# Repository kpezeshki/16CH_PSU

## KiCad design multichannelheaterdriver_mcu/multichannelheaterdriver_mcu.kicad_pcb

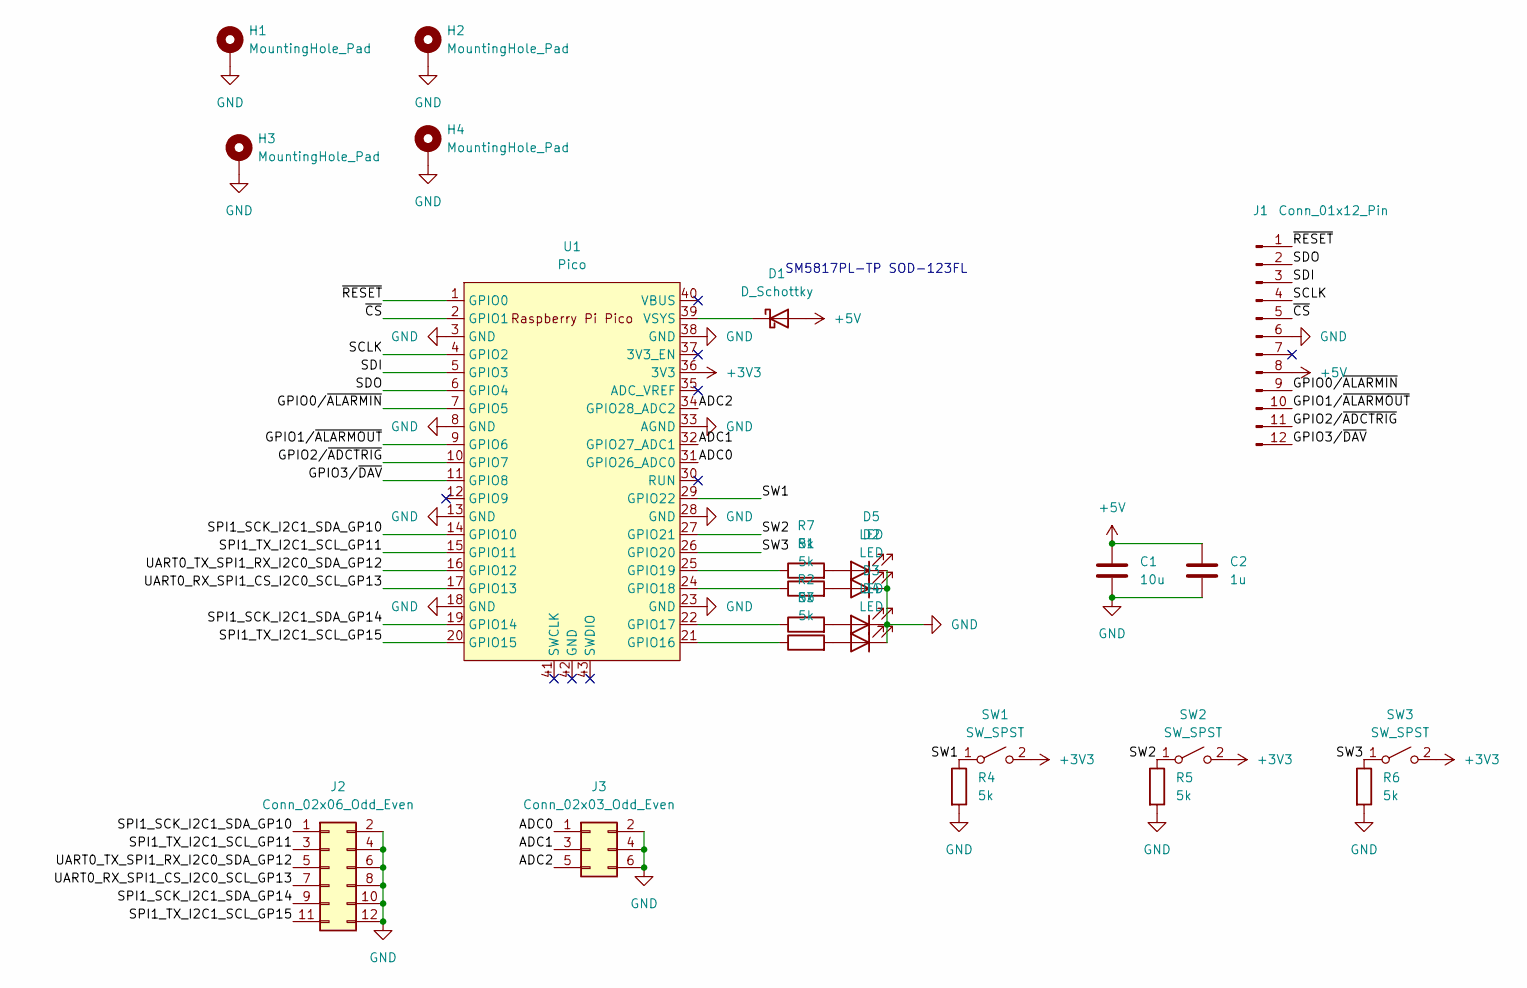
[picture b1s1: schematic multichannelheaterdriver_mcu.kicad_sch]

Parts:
C1: 10u; C_0805_2012Metric
C2: 1u; C_0805_2012Metric
D1: D_Schottky; D_SOD-123F
D2, D3, D4, D5: LED; LED_0805_2012Metric
H1, H2, H3, H4: MountingHole_Pad; MountingHole_3.2mm_M3_Pad
J1: Conn_01x12_Pin; PinHeader_1x12_P2.54mm_Vertical
J2: Conn_02x06_Odd_Even; PinHeader_2x06_P2.54mm_Horizontal
J3: Conn_02x03_Odd_Even; PinHeader_2x03_P2.54mm_Horizontal
R1, R2, R3, R4, R5, R6, R7: 5k; R_0805_2012Metric
SW1, SW2, SW3: SW_SPST; SW_Tactile_SPST_Angled_PTS645Vx31-2LFS
U1: Pico; RPi_Pico_SMD_TH

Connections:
+3V3: SW1.2 (B), SW2.2 (B), SW3.2 (B), U1.36 (3V3)
+5V: C1.1, C2.1, D1.2 (A), J1.8
/ADC0: J3.1, U1.31 (GPIO26_ADC0)
/ADC1: J3.3, U1.32 (GPIO27_ADC1)
/ADC2: J3.5, U1.34 (GPIO28_ADC2)
/GPIO0/~ALARMIN: J1.9, U1.7 (GPIO5)
/GPIO1/~ALARMOUT: J1.10, U1.9 (GPIO6)
/GPIO2/~ADCTRIG: J1.11, U1.10 (GPIO7)
/GPIO3/~DAV: J1.12, U1.11 (GPIO8)
/SCLK: J1.4, U1.4 (GPIO2)
/SDI: J1.3, U1.5 (GPIO3)
/SDO: J1.2, U1.6 (GPIO4)
/SPI1_SCK_I2C1_SDA_GP10: J2.1, U1.14 (GPIO10)
/SPI1_SCK_I2C1_SDA_GP14: J2.9, U1.19 (GPIO14)
/SPI1_TX_I2C1_SCL_GP11: J2.3, U1.15 (GPIO11)
/SPI1_TX_I2C1_SCL_GP15: J2.11, U1.20 (GPIO15)
/SW1: R4.1, SW1.1 (A), U1.29 (GPIO22)
/SW2: R5.1, SW2.1 (A), U1.27 (GPIO21)
/SW3: R6.1, SW3.1 (A), U1.26 (GPIO20)
/UART0_RX_SPI1_CS_I2C0_SCL_GP13: J2.7, U1.17 (GPIO13)
/UART0_TX_SPI1_RX_I2C0_SDA_GP12: J2.5, U1.16 (GPIO12)
/~CS: J1.5, U1.2 (GPIO1)
/~RESET: J1.1, U1.1 (GPIO0)
GND: C1.2, C2.2, D2.1 (K), D3.1 (K), D4.1 (K), D5.1 (K), H1.1, H2.1, H3.1, H4.1, J1.6, J2.2, J2.4, J2.6, J2.8, J2.10, J2.12, J3.2, J3.4, J3.6, R4.2, R5.2, R6.2, U1.3 (GND), U1.8 (GND), U1.13 (GND), U1.18 (GND), U1.23 (GND), U1.28 (GND), U1.33 (AGND), U1.38 (GND)
unnamed: D1.1 (K), U1.39 (VSYS)
unnamed: D2.2 (A), R1.2
unnamed: D3.2 (A), R2.2
unnamed: D4.2 (A), R3.2
unnamed: D5.2 (A), R7.2
unnamed: R3.1, U1.21 (GPIO16)
unnamed: R2.1, U1.22 (GPIO17)
unnamed: R1.1, U1.24 (GPIO18)
unnamed: R7.1, U1.25 (GPIO19)

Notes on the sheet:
SM5817PL-TP SOD-123FL

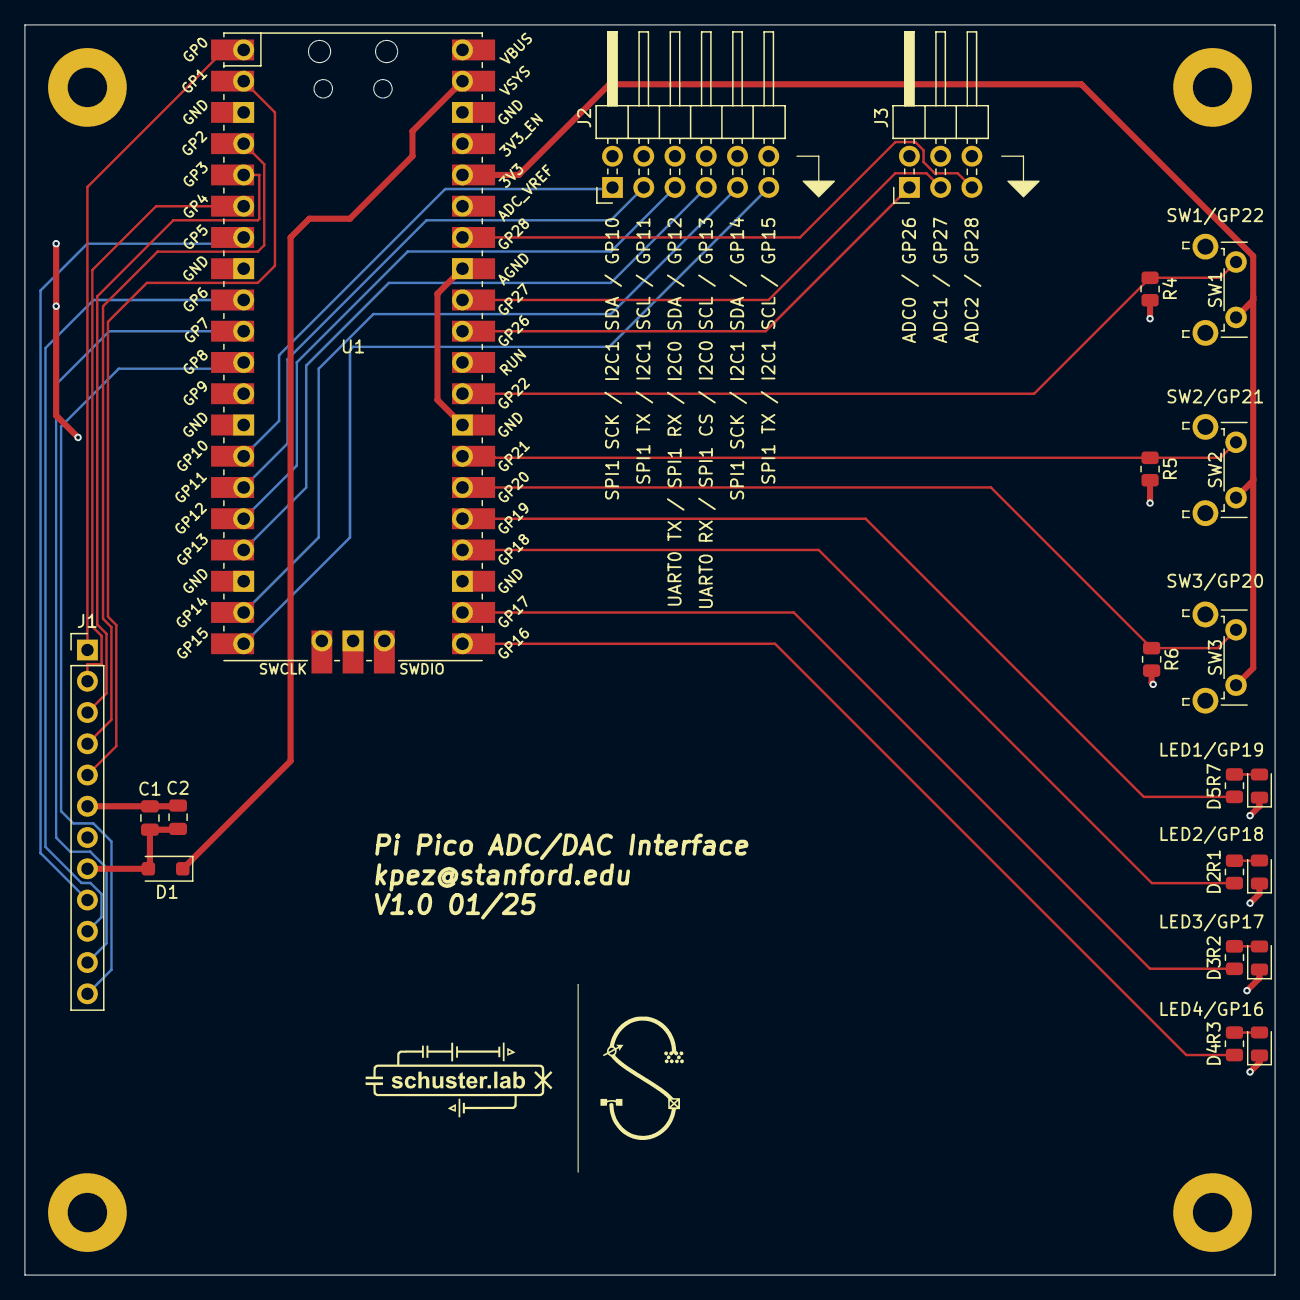
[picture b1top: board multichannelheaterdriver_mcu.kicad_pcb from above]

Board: 2 copper layers, 101.6 x 101.6 mm, 25 parts (0 on the bottom side), 33 nets.

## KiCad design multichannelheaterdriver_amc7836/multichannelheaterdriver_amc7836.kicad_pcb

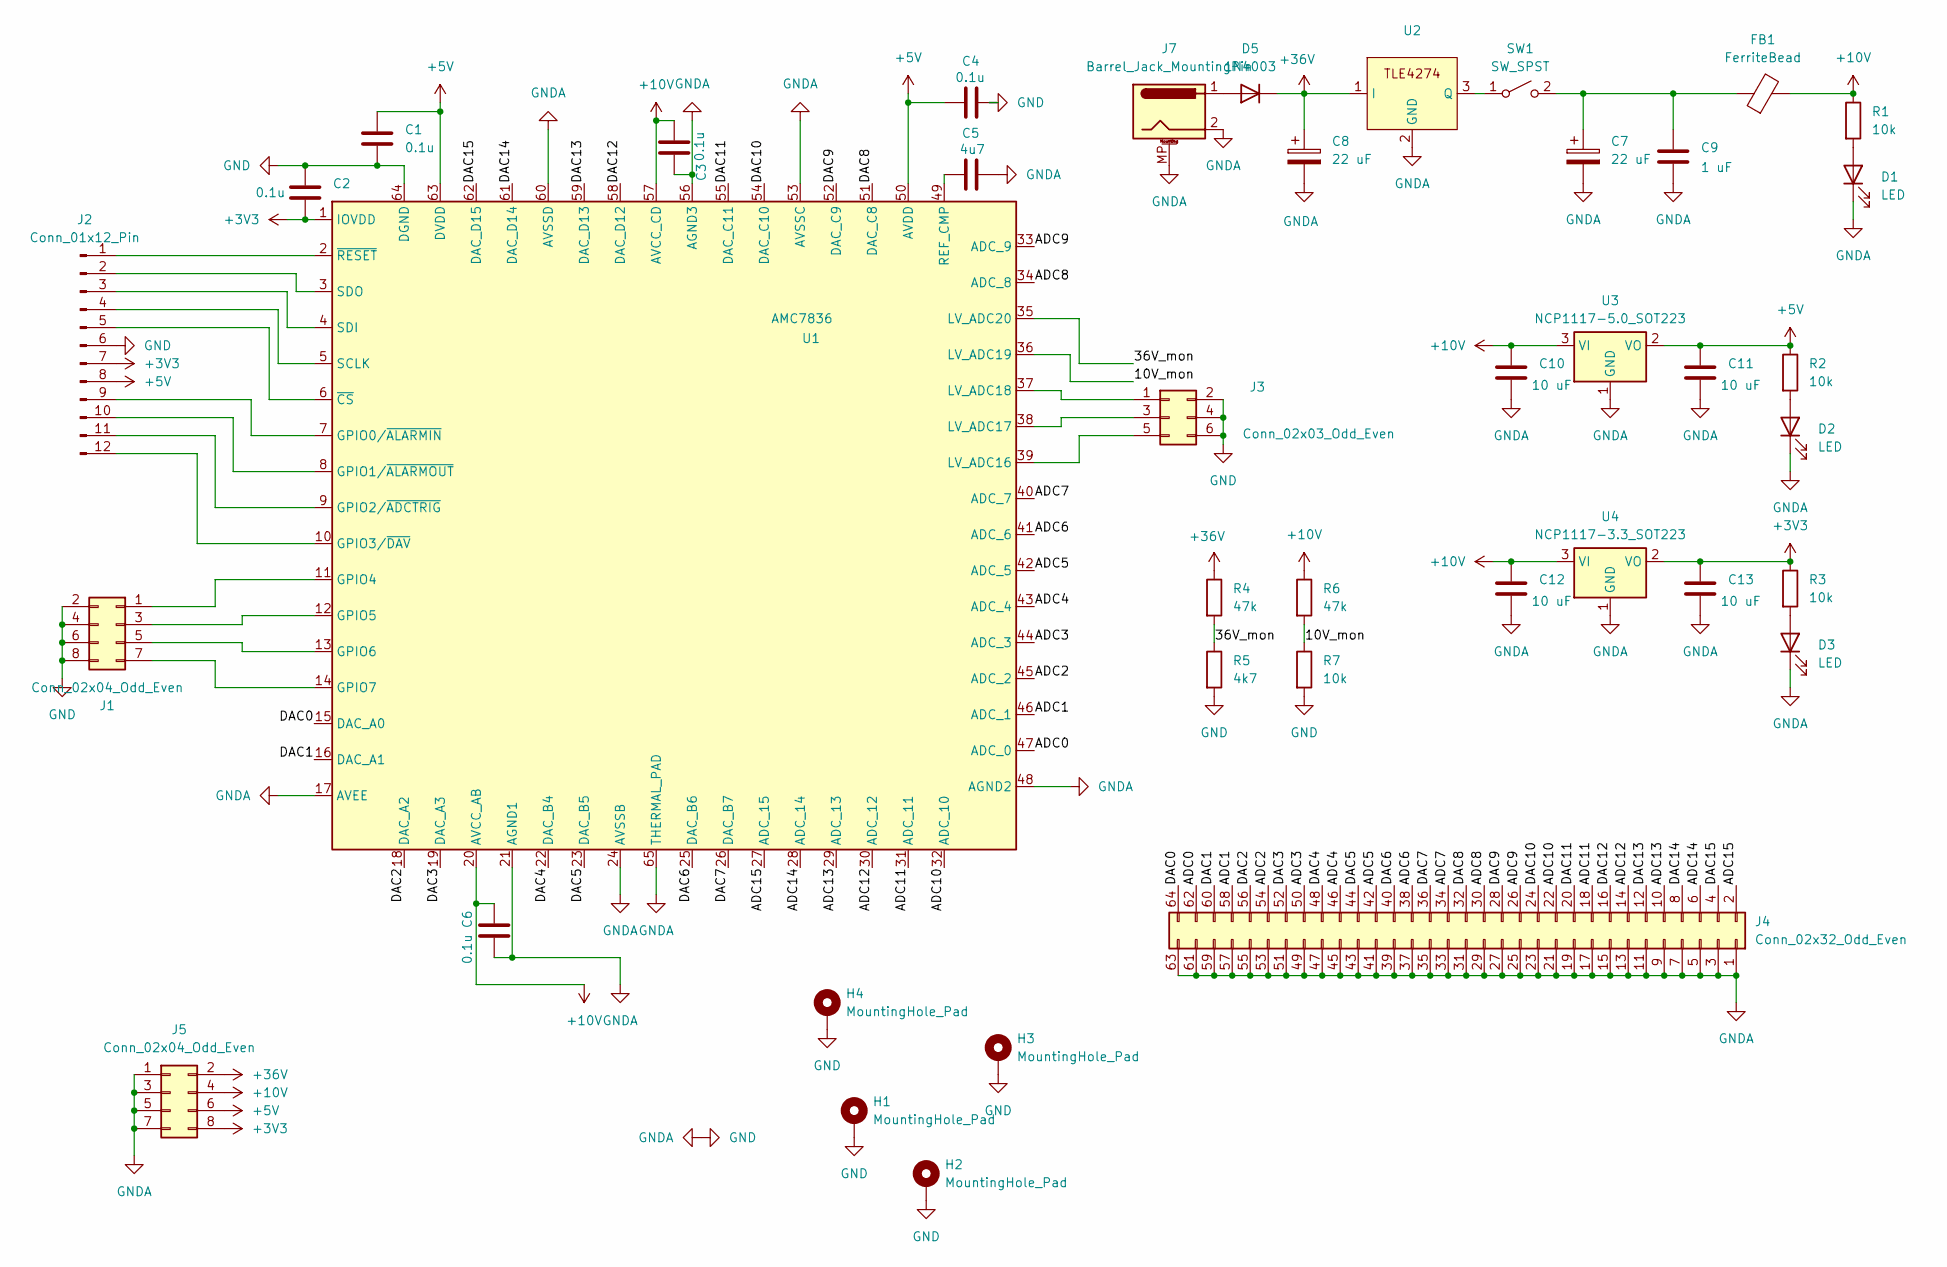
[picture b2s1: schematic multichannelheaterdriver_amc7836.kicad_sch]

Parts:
C1, C2, C3, C4, C6: 0.1u; C_0805_2012Metric
C5: 4u7; C_0805_2012Metric
C7, C8: 22 uF; CP_Radial_D6.3mm_P2.50mm
C9: 1 uF; C_0805_2012Metric
C10, C11, C12, C13: 10 uF; C_0805_2012Metric
D1, D2, D3: LED; LED_0805_2012Metric_Pad1.15x1.40mm_HandSolder
D5: 1N4003; D_DO-41_SOD81_P10.16mm_Horizontal
FB1: FerriteBead; R_0805_2012Metric
H1, H2, H3, H4: MountingHole_Pad; MountingHole_3.2mm_M3_Pad
J1: Conn_02x04_Odd_Even; PinHeader_2x04_P2.54mm_Horizontal
J2: Conn_01x12_Pin; PinHeader_1x12_P2.54mm_Vertical
J3: Conn_02x03_Odd_Even; PinHeader_2x03_P2.54mm_Horizontal
J4: Conn_02x32_Odd_Even; PinHeader_2x32_P2.54mm_Vertical
J5: Conn_02x04_Odd_Even; PinHeader_2x04_P2.54mm_Vertical
J7: Barrel_Jack_MountingPin; BarrelJack_CUI_PJ-063AH_Horizontal
R1, R2, R3, R7: 10k; R_0805_2012Metric
R4, R6: 47k; R_0805_2012Metric
R5: 4k7; R_0805_2012Metric
SW1: SW_SPST; PinHeader_1x02_P2.54mm_Horizontal
U1: AMC7836; IC_AMC7812BSPAP
U2: TO-252-3_TabPin2
U3: NCP1117-5.0_SOT223; SOT-223-3_TabPin2
U4: NCP1117-3.3_SOT223; SOT-223-3_TabPin2

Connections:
+3V3: C2.2, C13.1, J2.7, J5.8, R3.1, U1.1 (IOVDD), U4.2 (VO)
+5V: C1.1, C4.1, C11.1, J2.8, J5.6, R2.1, U1.50 (AVDD), U1.63 (DVDD), U3.2 (VO)
+10V: C3.1, C6.1, C10.1, C12.1, FB1.2, J5.4, R1.1, R6.1, U1.20 (AVCC_AB), U1.57 (AVCC_CD), U3.3 (VI), U4.3 (VI)
+36V: C8.1, D5.1 (K), J5.2, R4.1, U2.1 (I)
/10V_mon: R6.2, R7.1, U1.36 (LV_ADC19)
/36V_mon: R4.2, R5.1, U1.35 (LV_ADC20)
/ADC0: J4.62, U1.47 (ADC_0)
/ADC1: J4.58, U1.46 (ADC_1)
/ADC2: J4.54, U1.45 (ADC_2)
/ADC3: J4.50, U1.44 (ADC_3)
/ADC4: J4.46, U1.43 (ADC_4)
/ADC5: J4.42, U1.42 (ADC_5)
/ADC6: J4.38, U1.41 (ADC_6)
/ADC7: J4.34, U1.40 (ADC_7)
/ADC8: J4.30, U1.34 (ADC_8)
/ADC9: J4.26, U1.33 (ADC_9)
/ADC10: J4.22, U1.32 (ADC_10)
/ADC11: J4.18, U1.31 (ADC_11)
/ADC12: J4.14, U1.30 (ADC_12)
/ADC13: J4.10, U1.29 (ADC_13)
/ADC14: J4.6, U1.28 (ADC_14)
/ADC15: J4.2, U1.27 (ADC_15)
/DAC0: J4.64, U1.15 (DAC_A0)
/DAC1: J4.60, U1.16 (DAC_A1)
/DAC2: J4.56, U1.18 (DAC_A2)
/DAC3: J4.52, U1.19 (DAC_A3)
/DAC4: J4.48, U1.22 (DAC_B4)
/DAC5: J4.44, U1.23 (DAC_B5)
/DAC6: J4.40, U1.25 (DAC_B6)
/DAC7: J4.36, U1.26 (DAC_B7)
/DAC8: J4.32, U1.51 (DAC_C8)
/DAC9: J4.28, U1.52 (DAC_C9)
/DAC10: J4.24, U1.54 (DAC_C10)
/DAC11: J4.20, U1.55 (DAC_C11)
/DAC12: J4.16, U1.58 (DAC_D12)
/DAC13: J4.12, U1.59 (DAC_D13)
/DAC14: J4.8, U1.61 (DAC_D14)
/DAC15: J4.4, U1.62 (DAC_D15)
GND: C1.2, C2.1, C3.2, C4.2, C5.2, C6.2, C7.2, C8.2, C9.2, C10.2, C11.2, C12.2, C13.2, D1.1 (K), D2.1 (K), D3.1 (K), H1.1, H2.1, H3.1, H4.1, J1.2, J1.4, J1.6, J1.8, J2.6, J3.2, J3.4, J3.6, J4.1, J4.3, J4.5, J4.7, J4.9, J4.11, J4.13, J4.15, J4.17, J4.19, J4.21, J4.23, J4.25, J4.27, J4.29, J4.31, J4.33, J4.35, J4.37, J4.39, J4.41, J4.43, J4.45, J4.47, J4.49, J4.51, J4.53, J4.55, J4.57, J4.59, J4.61, J4.63, J5.1, J5.3, J5.5, J5.7, J7.2, J7.MP (MountPin), R5.2, R7.2, U1.17 (AVEE), U1.21 (AGND1), U1.24 (AVSSB), U1.48 (AGND2), U1.53 (AVSSC), U1.56 (AGND3), U1.60 (AVSSD), U1.64 (DGND), U1.65 (THERMAL_PAD), U2.2 (GND), U3.1 (GND), U4.1 (GND)
unnamed: D1.2 (A), R1.2
unnamed: D2.2 (A), R2.2
unnamed: D3.2 (A), R3.2
unnamed: D5.2 (A), J7.1
unnamed: J1.1, U1.11 (GPIO4)
unnamed: J1.3, U1.12 (GPIO5)
unnamed: J1.5, U1.13 (GPIO6)
unnamed: J1.7, U1.14 (GPIO7)
unnamed: J2.1, U1.2 (~RESET)
unnamed: J2.2, U1.3 (SDO)
unnamed: J2.3, U1.4 (SDI)
unnamed: J2.4, U1.5 (SCLK)
unnamed: J2.5, U1.6 (~CS)
unnamed: J2.9, U1.7 (GPIO0/~ALARMIN)
unnamed: J2.10, U1.8 (GPIO1/~ALARMOUT)
unnamed: J2.11, U1.9 (GPIO2/~ADCTRIG)
unnamed: J2.12, U1.10 (GPIO3/~DAV)
unnamed: J3.1, U1.37 (LV_ADC18)
unnamed: J3.3, U1.38 (LV_ADC17)
unnamed: J3.5, U1.39 (LV_ADC16)
unnamed: SW1.1 (A), U2.3 (Q)
unnamed: C7.1, C9.1, FB1.1, SW1.2 (B)
unnamed: C5.1, U1.49 (REF_CMP)

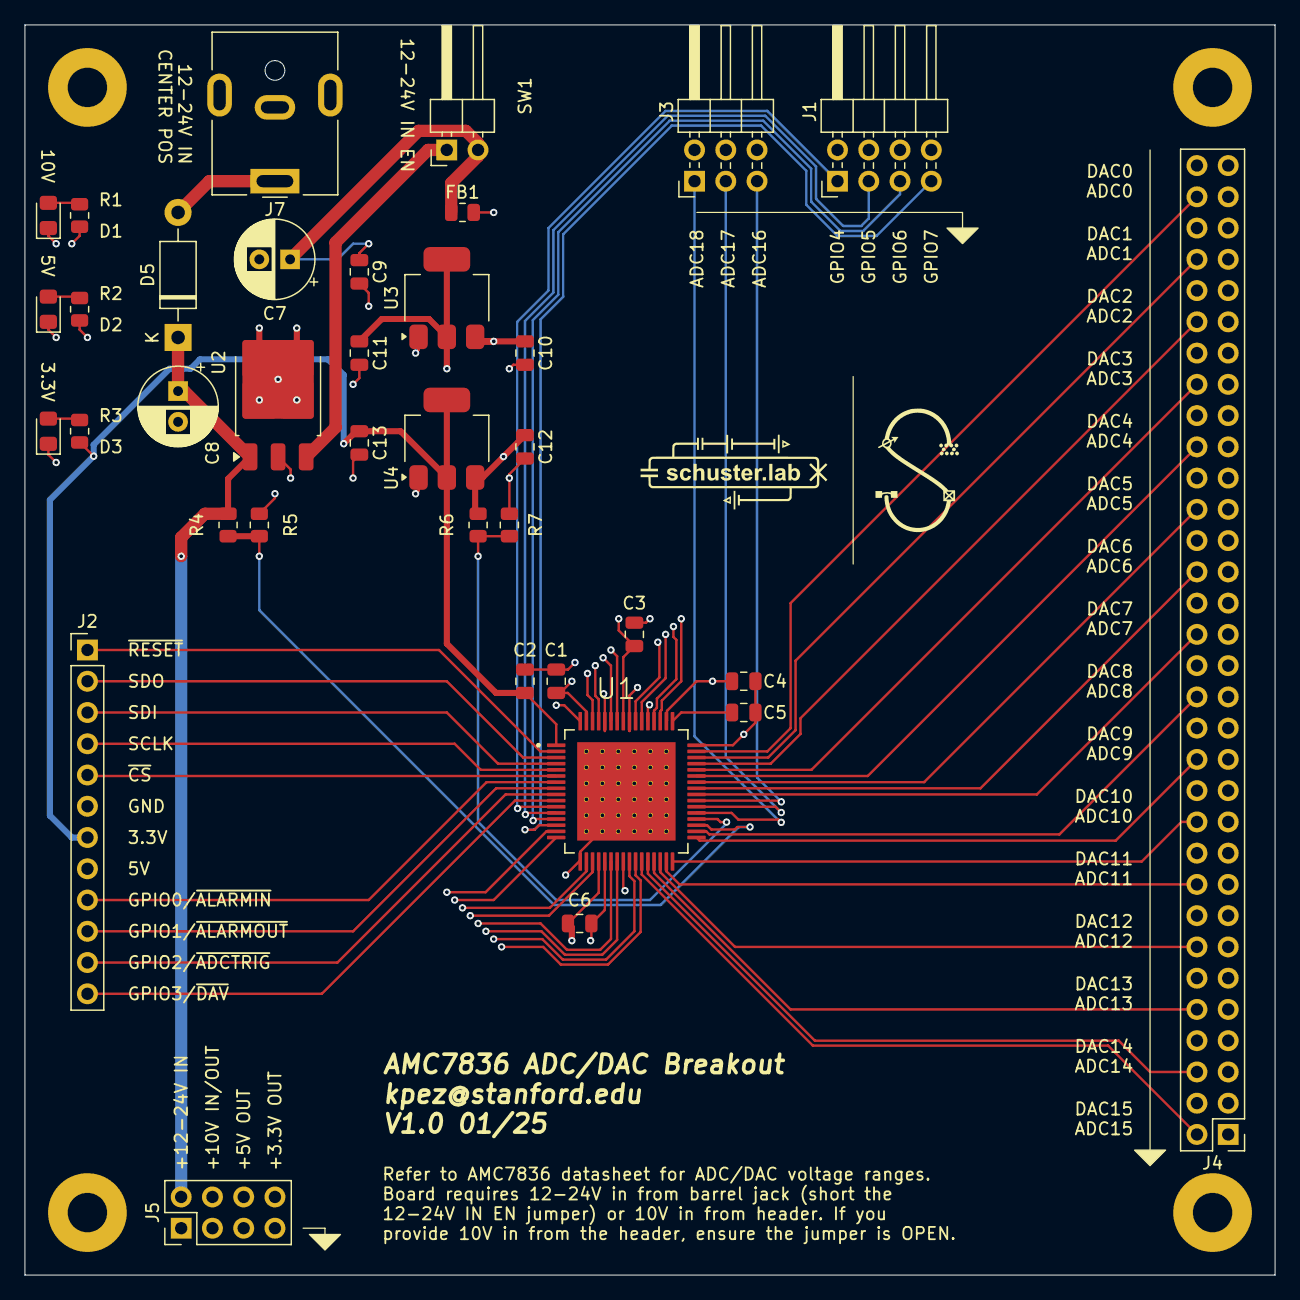
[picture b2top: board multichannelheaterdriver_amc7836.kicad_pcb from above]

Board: 6 copper layers, 101.6 x 101.6 mm, 40 parts (0 on the bottom side), 62 nets.

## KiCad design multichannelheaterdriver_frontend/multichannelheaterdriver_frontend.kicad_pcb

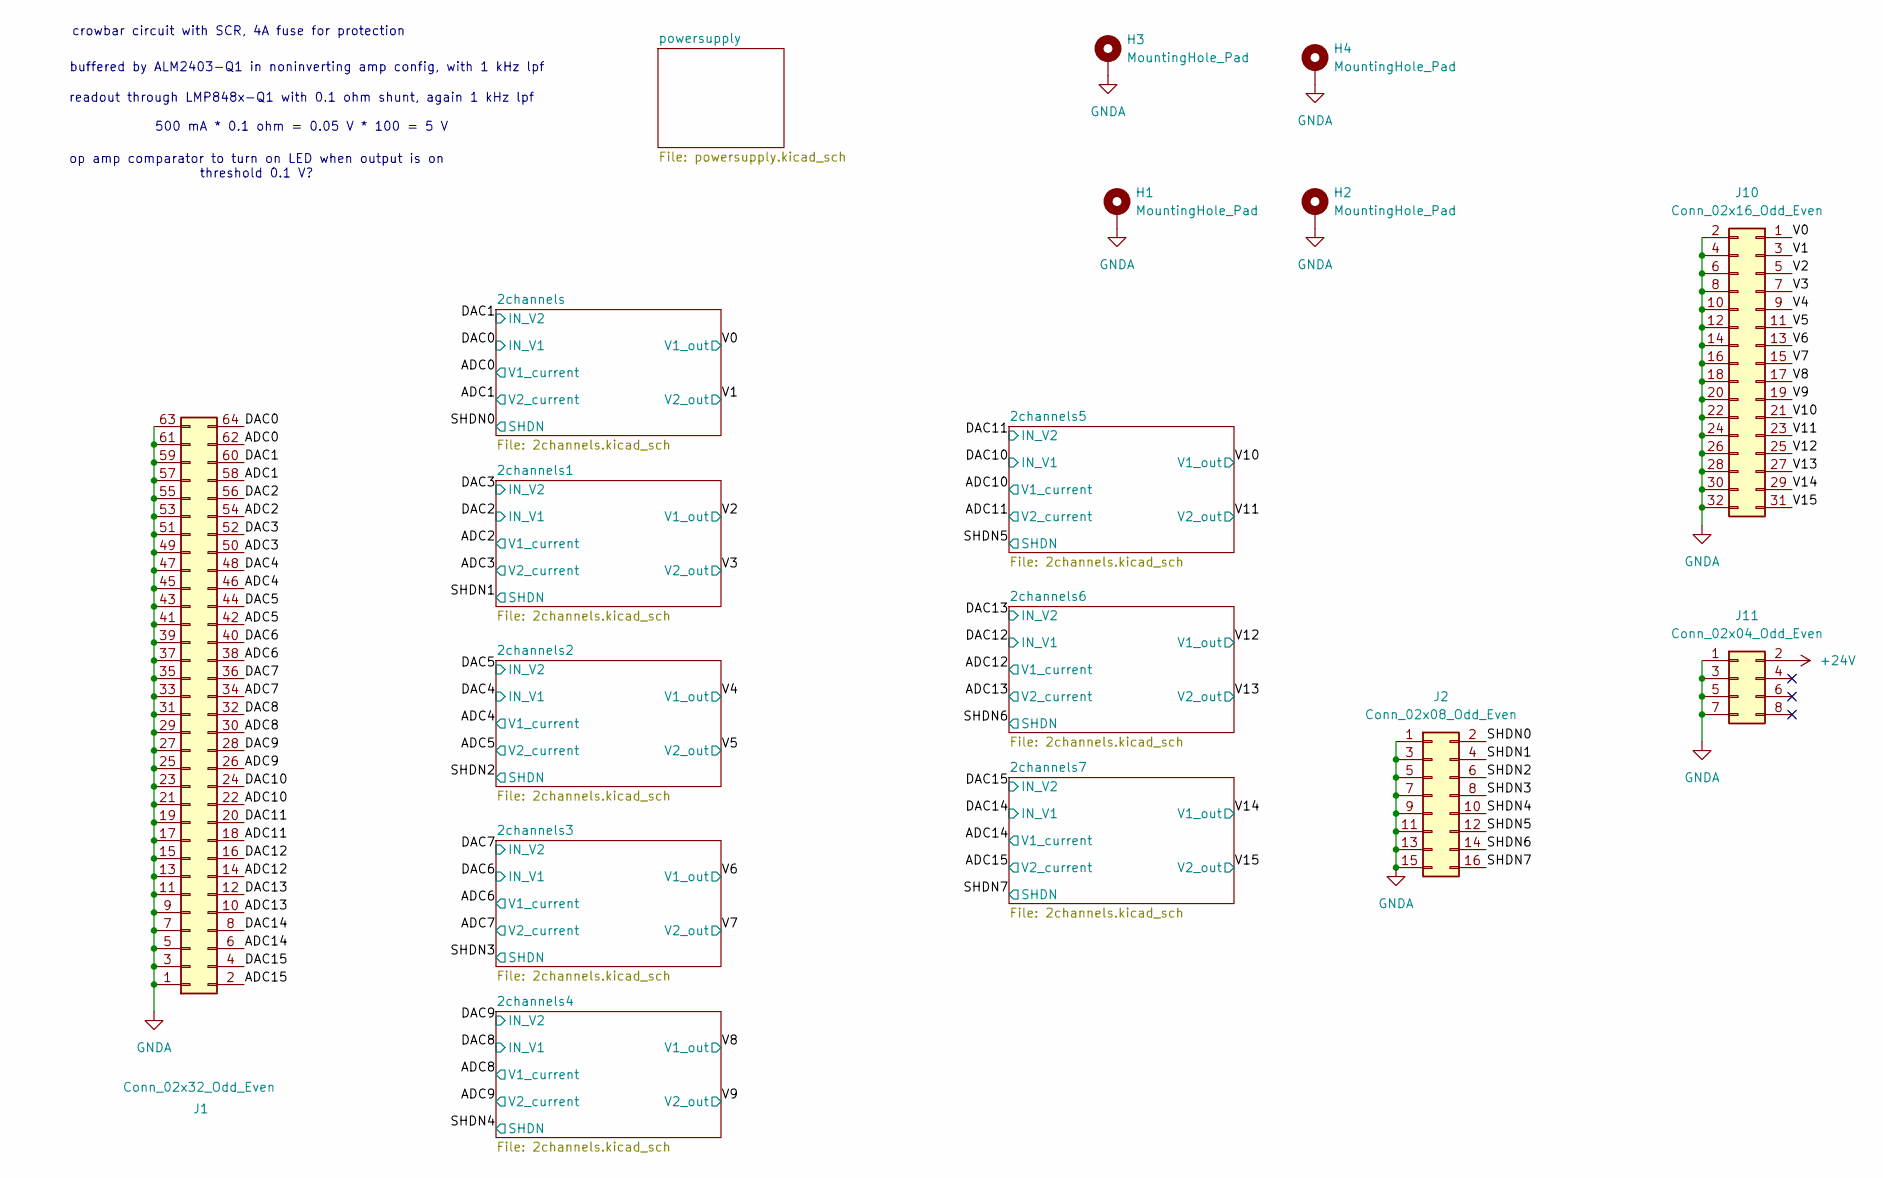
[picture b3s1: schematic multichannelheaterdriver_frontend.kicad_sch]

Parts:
H1, H2, H3, H4: MountingHole_Pad; MountingHole_3.2mm_M3_Pad
J1: Conn_02x32_Odd_Even; PinHeader_2x32_P2.54mm_Vertical
J2: Conn_02x08_Odd_Even; PinHeader_2x08_P2.54mm_Vertical
J10: Conn_02x16_Odd_Even; PinHeader_2x16_P2.54mm_Horizontal
J11: Conn_02x04_Odd_Even; PinHeader_2x04_P2.54mm_Vertical

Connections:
+24V: J11.2; also elsewhere on the board
/ADC0: J1.62; also elsewhere on the board
/ADC1: J1.58; also elsewhere on the board
/ADC2: J1.54; also elsewhere on the board
/ADC3: J1.50; also elsewhere on the board
/ADC4: J1.46; also elsewhere on the board
/ADC5: J1.42; also elsewhere on the board
/ADC6: J1.38; also elsewhere on the board
/ADC7: J1.34; also elsewhere on the board
/ADC8: J1.30; also elsewhere on the board
/ADC9: J1.26; also elsewhere on the board
/ADC10: J1.22; also elsewhere on the board
/ADC11: J1.18; also elsewhere on the board
/ADC12: J1.14; also elsewhere on the board
/ADC13: J1.10; also elsewhere on the board
/ADC14: J1.6; also elsewhere on the board
/ADC15: J1.2; also elsewhere on the board
/DAC0: J1.64; also elsewhere on the board
/DAC1: J1.60; also elsewhere on the board
/DAC2: J1.56; also elsewhere on the board
/DAC3: J1.52; also elsewhere on the board
/DAC4: J1.48; also elsewhere on the board
/DAC5: J1.44; also elsewhere on the board
/DAC6: J1.40; also elsewhere on the board
/DAC7: J1.36; also elsewhere on the board
/DAC8: J1.32; also elsewhere on the board
/DAC9: J1.28; also elsewhere on the board
/DAC10: J1.24; also elsewhere on the board
/DAC11: J1.20; also elsewhere on the board
/DAC12: J1.16; also elsewhere on the board
/DAC13: J1.12; also elsewhere on the board
/DAC14: J1.8; also elsewhere on the board
/DAC15: J1.4; also elsewhere on the board
/SHDN0: J2.2; also elsewhere on the board
/SHDN1: J2.4; also elsewhere on the board
/SHDN2: J2.6; also elsewhere on the board
/SHDN3: J2.8; also elsewhere on the board
/SHDN4: J2.10; also elsewhere on the board
/SHDN5: J2.12; also elsewhere on the board
/SHDN6: J2.14; also elsewhere on the board
/SHDN7: J2.16; also elsewhere on the board
/V0: J10.1; also elsewhere on the board
/V1: J10.3; also elsewhere on the board
/V2: J10.5; also elsewhere on the board
/V3: J10.7; also elsewhere on the board
/V4: J10.9; also elsewhere on the board
/V5: J10.11; also elsewhere on the board
/V6: J10.13; also elsewhere on the board
/V7: J10.15; also elsewhere on the board
/V8: J10.17; also elsewhere on the board
/V9: J10.19; also elsewhere on the board
/V10: J10.21; also elsewhere on the board
/V11: J10.23; also elsewhere on the board
/V12: J10.25; also elsewhere on the board
/V13: J10.27; also elsewhere on the board
/V14: J10.29; also elsewhere on the board
/V15: J10.31; also elsewhere on the board
GNDA: H1.1, H2.1, H3.1, H4.1, J1.1, J1.3, J1.5, J1.7, J1.9, J1.11, J1.13, J1.15, J1.17, J1.19, J1.21, J1.23, J1.25, J1.27, J1.29, J1.31, J1.33, J1.35, J1.37, J1.39, J1.41, J1.43, J1.45, J1.47, J1.49, J1.51, J1.53, J1.55, J1.57, J1.59, J1.61, J1.63, J2.1, J2.3, J2.5, J2.7, J2.9, J2.11, J2.13, J2.15, J10.2, J10.4, J10.6, J10.8, J10.10, J10.12, J10.14, J10.16, J10.18, J10.20, J10.22, J10.24, J10.26, J10.28, J10.30, J10.32, J11.1, J11.3, J11.5, J11.7; also elsewhere on the board

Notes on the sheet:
op amp comparator to turn on LED when output is on threshold 0.1 V?
buffered by ALM2403-Q1 in noninverting amp config, with 1 kHz lpf
crowbar circuit with SCR, 4A fuse for protection
readout through LMP848x-Q1 with 0.1 ohm shunt, again 1 kHz lpf 500 mA * 0.1 ohm = 0.05 V * 100 = 5 V

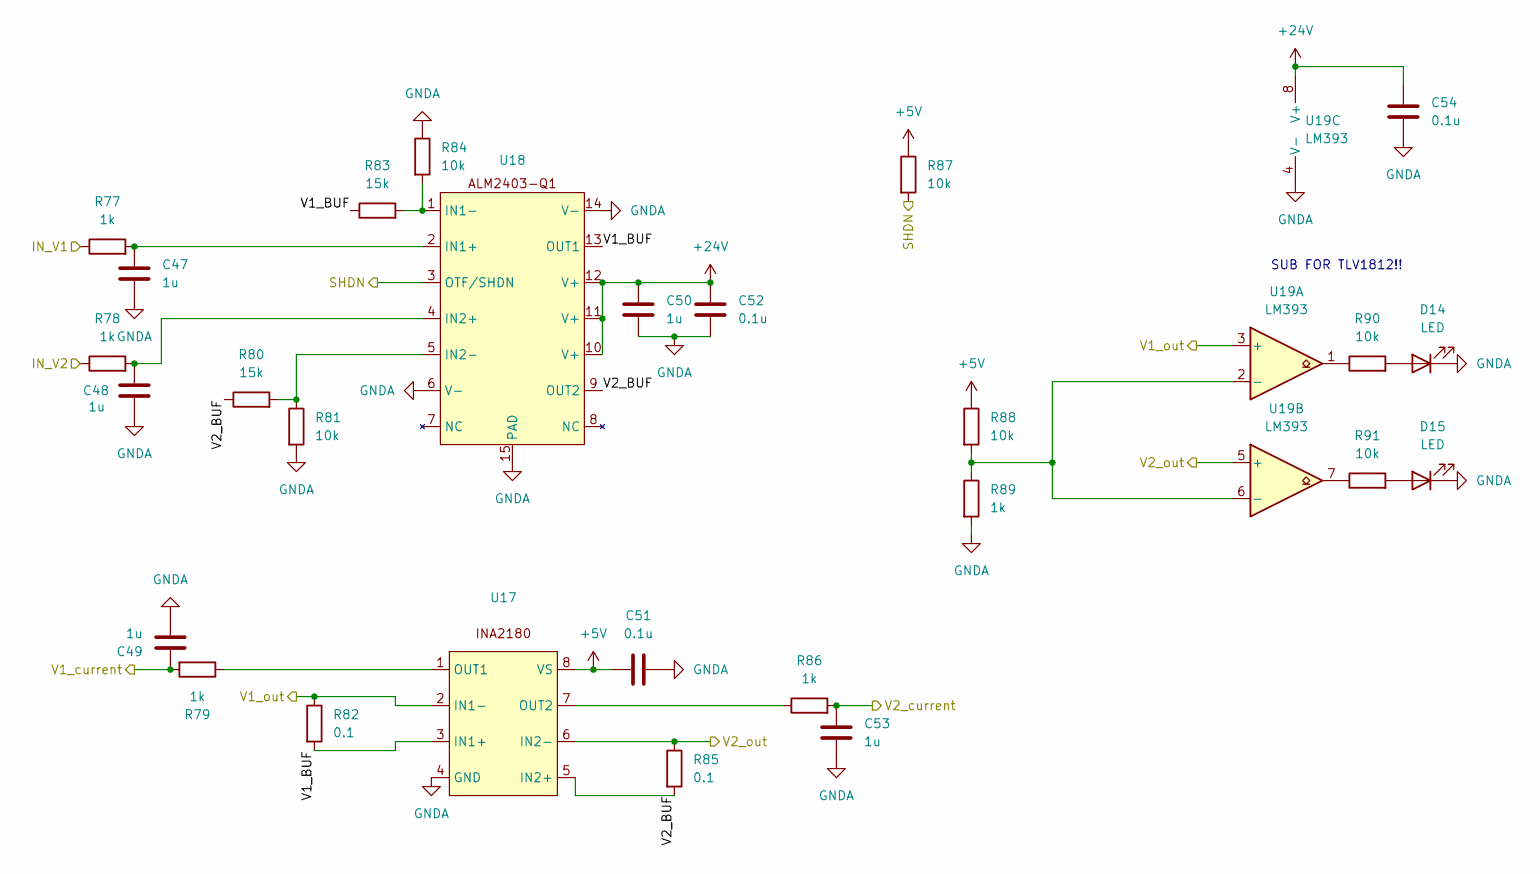
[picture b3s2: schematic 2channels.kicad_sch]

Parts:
C47, C48, C49, C50, C53: 1u; C_0603_1608Metric
C51, C52, C54: 0.1u; C_0603_1608Metric
D14, D15: LED; LED_0805_2012Metric
R77, R78, R79, R86, R89: 1k; R_0603_1608Metric
R80, R83: 15k; R_0603_1608Metric
R81, R84, R87, R88, R90, R91: 10k; R_0603_1608Metric
R82, R85: 0.1; R_0603_1608Metric
U17: VSSOP-8_3x3mm_P0.65mm
U18: IC_TPS27S100BPWPR
U19: LM393; SOIC-8_3.9x4.9mm_P1.27mm

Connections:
+5V: C51.1, R87.1, R88.1, U17.8 (VS); also elsewhere on the board
+24V: C50.1, C52.1, C54.1, U18.10 (V+), U18.11 (V+), U18.12 (V+), U19.8 (V+); also elsewhere on the board
/2channels5/V1_BUF: R82.2, R83.1, U17.3 (IN1+), U18.13 (OUT1)
/2channels5/V2_BUF: R80.1, R85.2, U17.5 (IN2+), U18.9 (OUT2)
/ADC10: C49.1, R79.2; also elsewhere on the board
/ADC11: C53.1, R86.2; also elsewhere on the board
/DAC10: R77.1; also elsewhere on the board
/DAC11: R78.1; also elsewhere on the board
/SHDN5: R87.2, U18.3 (OTF/SHDN); also elsewhere on the board
/V10: R82.1, U17.2 (IN1-), U19.3 (+); also elsewhere on the board
/V11: R85.1, U17.6 (IN2-), U19.5 (+); also elsewhere on the board
GNDA: C47.2, C48.2, C49.2, C50.2, C51.2, C52.2, C53.2, C54.2, D14.1 (K), D15.1 (K), R81.2, R84.1, R89.2, U17.4 (GND), U18.6 (V-), U18.14 (V-), U18.15 (PAD), U19.4 (V-); also elsewhere on the board
unnamed: D14.2 (A), R90.2
unnamed: D15.2 (A), R91.2
unnamed: R90.1, U19.1
unnamed: R91.1, U19.7
unnamed: R79.1, U17.1 (OUT1)
unnamed: R86.1, U17.7 (OUT2)
unnamed: C47.1, R77.2, U18.2 (IN1+)
unnamed: R83.2, R84.2, U18.1 (IN1-)
unnamed: C48.1, R78.2, U18.4 (IN2+)
unnamed: R80.2, R81.1, U18.5 (IN2-)
unnamed: R88.2, R89.1, U19.2 (-), U19.6 (-)

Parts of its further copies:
C7, C8, C9, C10, C13, C15, C16, C17, C18, C21, C23, C24, C25, C26, C29, C31, C32, C33, C34, C37, C39, C40, C41, C42, C45, C55, C56, C57, C58, C61, C63, C64, C65, C66, C69: 1u; C_0603_1608Metric
C11, C12, C14, C19, C20, C22, C27, C28, C30, C35, C36, C38, C43, C44, C46, C59, C60, C62, C67, C68, C70: 0.1u; C_0603_1608Metric
D4, D5, D6, D7, D8, D9, D10, D11, D12, D13, D16, D17, D18, D19: LED; LED_0805_2012Metric
R2, R3, R4, R11, R14, R17, R18, R19, R26, R29, R32, R33, R34, R41, R44, R47, R48, R49, R56, R59, R62, R63, R64, R71, R74, R92, R93, R94, R101, R104, R107, R108, R109, R116, R119: 1k; R_0603_1608Metric
R5, R8, R20, R23, R35, R38, R50, R53, R65, R68, R95, R98, R110, R113: 15k; R_0603_1608Metric
R6, R9, R12, R13, R15, R16, R21, R24, R27, R28, R30, R31, R36, R39, R42, R43, R45, R46, R51, R54, R57, R58, R60, R61, R66, R69, R72, R73, R75, R76, R96, R99, R102, R103, R105, R106, R111, R114, R117, R118, R120, R121: 10k; R_0603_1608Metric
R7, R10, R22, R25, R37, R40, R52, R55, R67, R70, R97, R100, R112, R115: 0.1; R_0603_1608Metric
U2, U5, U8, U11, U14, U20, U23: VSSOP-8_3x3mm_P0.65mm
U3, U6, U9, U12, U15, U21, U24: IC_TPS27S100BPWPR
U4, U7, U10, U13, U16, U22, U25: LM393; SOIC-8_3.9x4.9mm_P1.27mm

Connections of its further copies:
+5V: C11.1, C19.1, C27.1, C35.1, C43.1, C59.1, C67.1, R12.1, R13.1, R27.1, R28.1, R42.1, R43.1, R57.1, R58.1, R72.1, R73.1, R102.1, R103.1, R117.1, R118.1, U2.8 (VS), U5.8 (VS), U8.8 (VS), U11.8 (VS), U14.8 (VS), U20.8 (VS), U23.8 (VS); also elsewhere on the board
+24V: C10.1, C12.1, C14.1, C18.1, C20.1, C22.1, C26.1, C28.1, C30.1, C34.1, C36.1, C38.1, C42.1, C44.1, C46.1, C58.1, C60.1, C62.1, C66.1, C68.1, C70.1, U3.10 (V+), U3.11 (V+), U3.12 (V+), U4.8 (V+), U6.10 (V+), U6.11 (V+), U6.12 (V+), U7.8 (V+), U9.10 (V+), U9.11 (V+), U9.12 (V+), U10.8 (V+), U12.10 (V+), U12.11 (V+), U12.12 (V+), U13.8 (V+), U15.10 (V+), U15.11 (V+), U15.12 (V+), U16.8 (V+), U21.10 (V+), U21.11 (V+), U21.12 (V+), U22.8 (V+), U24.10 (V+), U24.11 (V+), U24.12 (V+), U25.8 (V+); also elsewhere on the board
/2channels1/V1_BUF: R22.2, R23.1, U5.3 (IN1+), U6.13 (OUT1)
/2channels1/V2_BUF: R20.1, R25.2, U5.5 (IN2+), U6.9 (OUT2)
/2channels2/V1_BUF: R37.2, R38.1, U8.3 (IN1+), U9.13 (OUT1)
/2channels2/V2_BUF: R35.1, R40.2, U8.5 (IN2+), U9.9 (OUT2)
/2channels3/V1_BUF: R52.2, R53.1, U11.3 (IN1+), U12.13 (OUT1)
/2channels3/V2_BUF: R50.1, R55.2, U11.5 (IN2+), U12.9 (OUT2)
/2channels4/V1_BUF: R67.2, R68.1, U14.3 (IN1+), U15.13 (OUT1)
/2channels4/V2_BUF: R65.1, R70.2, U14.5 (IN2+), U15.9 (OUT2)
/2channels6/V1_BUF: R97.2, R98.1, U20.3 (IN1+), U21.13 (OUT1)
/2channels6/V2_BUF: R95.1, R100.2, U20.5 (IN2+), U21.9 (OUT2)
/2channels7/V1_BUF: R112.2, R113.1, U23.3 (IN1+), U24.13 (OUT1)
/2channels7/V2_BUF: R110.1, R115.2, U23.5 (IN2+), U24.9 (OUT2)
/2channels/V1_BUF: R7.2, R8.1, U2.3 (IN1+), U3.13 (OUT1)
/2channels/V2_BUF: R5.1, R10.2, U2.5 (IN2+), U3.9 (OUT2)
/ADC0: C9.1, R4.2; also elsewhere on the board
/ADC1: C13.1, R11.2; also elsewhere on the board
/ADC2: C17.1, R19.2; also elsewhere on the board
/ADC3: C21.1, R26.2; also elsewhere on the board
/ADC4: C25.1, R34.2; also elsewhere on the board
/ADC5: C29.1, R41.2; also elsewhere on the board
/ADC6: C33.1, R49.2; also elsewhere on the board
/ADC7: C37.1, R56.2; also elsewhere on the board
/ADC8: C41.1, R64.2; also elsewhere on the board
/ADC9: C45.1, R71.2; also elsewhere on the board
/ADC12: C57.1, R94.2; also elsewhere on the board
/ADC13: C61.1, R101.2; also elsewhere on the board
/ADC14: C65.1, R109.2; also elsewhere on the board
/ADC15: C69.1, R116.2; also elsewhere on the board
/DAC0: R2.1; also elsewhere on the board
/DAC1: R3.1; also elsewhere on the board
/DAC2: R17.1; also elsewhere on the board
/DAC3: R18.1; also elsewhere on the board
/DAC4: R32.1; also elsewhere on the board
/DAC5: R33.1; also elsewhere on the board
/DAC6: R47.1; also elsewhere on the board
/DAC7: R48.1; also elsewhere on the board
/DAC8: R62.1; also elsewhere on the board
/DAC9: R63.1; also elsewhere on the board
/DAC12: R92.1; also elsewhere on the board
/DAC13: R93.1; also elsewhere on the board
/DAC14: R107.1; also elsewhere on the board
/DAC15: R108.1; also elsewhere on the board
/SHDN0: R12.2, U3.3 (OTF/SHDN); also elsewhere on the board
/SHDN1: R27.2, U6.3 (OTF/SHDN); also elsewhere on the board
/SHDN2: R42.2, U9.3 (OTF/SHDN); also elsewhere on the board
/SHDN3: R57.2, U12.3 (OTF/SHDN); also elsewhere on the board
/SHDN4: R72.2, U15.3 (OTF/SHDN); also elsewhere on the board
/SHDN6: R102.2, U21.3 (OTF/SHDN); also elsewhere on the board
/SHDN7: R117.2, U24.3 (OTF/SHDN); also elsewhere on the board
/V0: R7.1, U2.2 (IN1-), U4.3 (+); also elsewhere on the board
/V1: R10.1, U2.6 (IN2-), U4.5 (+); also elsewhere on the board
/V2: R22.1, U5.2 (IN1-), U7.3 (+); also elsewhere on the board
/V3: R25.1, U5.6 (IN2-), U7.5 (+); also elsewhere on the board
/V4: R37.1, U8.2 (IN1-), U10.3 (+); also elsewhere on the board
/V5: R40.1, U8.6 (IN2-), U10.5 (+); also elsewhere on the board
/V6: R52.1, U11.2 (IN1-), U13.3 (+); also elsewhere on the board
/V7: R55.1, U11.6 (IN2-), U13.5 (+); also elsewhere on the board
/V8: R67.1, U14.2 (IN1-), U16.3 (+); also elsewhere on the board
/V9: R70.1, U14.6 (IN2-), U16.5 (+); also elsewhere on the board
/V12: R97.1, U20.2 (IN1-), U22.3 (+); also elsewhere on the board
/V13: R100.1, U20.6 (IN2-), U22.5 (+); also elsewhere on the board
/V14: R112.1, U23.2 (IN1-), U25.3 (+); also elsewhere on the board
/V15: R115.1, U23.6 (IN2-), U25.5 (+); also elsewhere on the board
GNDA: C7.2, C8.2, C9.2, C10.2, C11.2, C12.2, C13.2, C14.2, C15.2, C16.2, C17.2, C18.2, C19.2, C20.2, C21.2, C22.2, C23.2, C24.2, C25.2, C26.2, C27.2, C28.2, C29.2, C30.2, C31.2, C32.2, C33.2, C34.2, C35.2, C36.2, C37.2, C38.2, C39.2, C40.2, C41.2, C42.2, C43.2, C44.2, C45.2, C46.2, C55.2, C56.2, C57.2, C58.2, C59.2, C60.2, C61.2, C62.2, C63.2, C64.2, C65.2, C66.2, C67.2, C68.2, C69.2, C70.2, D4.1 (K), D5.1 (K), D6.1 (K), D7.1 (K), D8.1 (K), D9.1 (K), D10.1 (K), D11.1 (K), D12.1 (K), D13.1 (K), D16.1 (K), D17.1 (K), D18.1 (K), D19.1 (K), R6.2, R9.1, R14.2, R21.2, R24.1, R29.2, R36.2, R39.1, R44.2, R51.2, R54.1, R59.2, R66.2, R69.1, R74.2, R96.2, R99.1, R104.2, R111.2, R114.1, R119.2, U2.4 (GND), U3.6 (V-), U3.14 (V-), U3.15 (PAD), U4.4 (V-), U5.4 (GND), U6.6 (V-), U6.14 (V-), U6.15 (PAD), U7.4 (V-), U8.4 (GND), U9.6 (V-), U9.14 (V-), U9.15 (PAD), U10.4 (V-), U11.4 (GND), U12.6 (V-), U12.14 (V-), U12.15 (PAD), U13.4 (V-), U14.4 (GND), U15.6 (V-), U15.14 (V-), U15.15 (PAD), U16.4 (V-), U20.4 (GND), U21.6 (V-), U21.14 (V-), U21.15 (PAD), U22.4 (V-), U23.4 (GND), U24.6 (V-), U24.14 (V-), U24.15 (PAD), U25.4 (V-); also elsewhere on the board
unnamed: D4.2 (A), R15.2
unnamed: D5.2 (A), R16.2
unnamed: D6.2 (A), R30.2
unnamed: D7.2 (A), R31.2
unnamed: D8.2 (A), R45.2
unnamed: D9.2 (A), R46.2
unnamed: D10.2 (A), R60.2
unnamed: D11.2 (A), R61.2
unnamed: D12.2 (A), R75.2
unnamed: D13.2 (A), R76.2
unnamed: D16.2 (A), R105.2
unnamed: D17.2 (A), R106.2
unnamed: D18.2 (A), R120.2
unnamed: D19.2 (A), R121.2
unnamed: R15.1, U4.1
unnamed: R16.1, U4.7
unnamed: R30.1, U7.1
unnamed: R31.1, U7.7
unnamed: R45.1, U10.1
unnamed: R46.1, U10.7
unnamed: R60.1, U13.1
unnamed: R61.1, U13.7
unnamed: R75.1, U16.1
unnamed: R76.1, U16.7
unnamed: R105.1, U22.1
unnamed: R106.1, U22.7
unnamed: R120.1, U25.1
unnamed: R121.1, U25.7
unnamed: R4.1, U2.1 (OUT1)
unnamed: R11.1, U2.7 (OUT2)
unnamed: C7.1, R2.2, U3.2 (IN1+)
unnamed: R8.2, R9.2, U3.1 (IN1-)
unnamed: C8.1, R3.2, U3.4 (IN2+)
unnamed: R5.2, R6.1, U3.5 (IN2-)
unnamed: R13.2, R14.1, U4.2 (-), U4.6 (-)
unnamed: R19.1, U5.1 (OUT1)
unnamed: R26.1, U5.7 (OUT2)
unnamed: C15.1, R17.2, U6.2 (IN1+)
unnamed: R23.2, R24.2, U6.1 (IN1-)
unnamed: C16.1, R18.2, U6.4 (IN2+)
unnamed: R20.2, R21.1, U6.5 (IN2-)
unnamed: R28.2, R29.1, U7.2 (-), U7.6 (-)
unnamed: R34.1, U8.1 (OUT1)
unnamed: R41.1, U8.7 (OUT2)
unnamed: C23.1, R32.2, U9.2 (IN1+)
unnamed: R38.2, R39.2, U9.1 (IN1-)
unnamed: C24.1, R33.2, U9.4 (IN2+)
unnamed: R35.2, R36.1, U9.5 (IN2-)
unnamed: R43.2, R44.1, U10.2 (-), U10.6 (-)
unnamed: R49.1, U11.1 (OUT1)
unnamed: R56.1, U11.7 (OUT2)
unnamed: C31.1, R47.2, U12.2 (IN1+)
unnamed: R53.2, R54.2, U12.1 (IN1-)
unnamed: C32.1, R48.2, U12.4 (IN2+)
unnamed: R50.2, R51.1, U12.5 (IN2-)
unnamed: R58.2, R59.1, U13.2 (-), U13.6 (-)
unnamed: R64.1, U14.1 (OUT1)
unnamed: R71.1, U14.7 (OUT2)
unnamed: C39.1, R62.2, U15.2 (IN1+)
unnamed: R68.2, R69.2, U15.1 (IN1-)
unnamed: C40.1, R63.2, U15.4 (IN2+)
unnamed: R65.2, R66.1, U15.5 (IN2-)
unnamed: R73.2, R74.1, U16.2 (-), U16.6 (-)
unnamed: R94.1, U20.1 (OUT1)
unnamed: R101.1, U20.7 (OUT2)
unnamed: C55.1, R92.2, U21.2 (IN1+)
unnamed: R98.2, R99.2, U21.1 (IN1-)
unnamed: C56.1, R93.2, U21.4 (IN2+)
unnamed: R95.2, R96.1, U21.5 (IN2-)
unnamed: R103.2, R104.1, U22.2 (-), U22.6 (-)
unnamed: R109.1, U23.1 (OUT1)
unnamed: R116.1, U23.7 (OUT2)
unnamed: C63.1, R107.2, U24.2 (IN1+)
unnamed: R113.2, R114.2, U24.1 (IN1-)
unnamed: C64.1, R108.2, U24.4 (IN2+)
unnamed: R110.2, R111.1, U24.5 (IN2-)
unnamed: R118.2, R119.1, U25.2 (-), U25.6 (-)

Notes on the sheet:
SUB FOR TLV1812!!
